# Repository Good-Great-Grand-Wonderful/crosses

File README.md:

> [!NOTE]
> This repo is for historical purposes. Crosses has iterated and is now on [V2](https://github.com/Good-Great-Grand-Wonderful/crosses-v2)

# Crosses

### Gerbers

Production ready and prepped with JLCPCB part numbers: [Gerbers](Gerbers)

### BOM

#### Cases

N = Number of trackballs

| Qty       |3x5 | 3x6 | 4x6 | Item                                              | Notes                             |
|-----------|----|-----|-----|---------------------------------------------------|-----------------------------------|
| 24        | x  | x   | x   | M3 Heat set inserts                               |                                   |
| 16        | x  | x   | x   | M3 x 5mm Hex Bolts                                | +2 for every trackball you delete |
| 2xN       | x  | x   | x   | M3 x 12mm Hex Bolts                               |                                   |
| 2xN       | x  | x   | x   | M3 x 8mm Hex Bolts                                |                                   |
| 1         | x  | x   | x   | Thumb Cluster PCB Panel                           |                                   |
| 4         | x  | x   | x   | Hirose FH12-14S 0.5SH 1x14 1MP P0.50mm Horizontal |                                   |
| 2         | x  | x   | x   | SM06B-SRSS-TB(LF)(SN)                             |                                   |
| 1         | x  |     |     | 3x5 Matrix PCB Panel                              |                                   |
| 1         |    | x   |     | 3x6 Matrix PCB Panel                              |                                   |
| 1         |    |     | x   | 4x6 Matrix PCB Panel                              |                                   |
| 2         | x  | x   | x   | 150mm 14p 0.5mm pitch FFC cables                  |                                   |
| 1xN       | x  | x   | x   | 100mm 6p JST SH 1.0 Same direction cables         |                                   |
| 2x        | x  | x   | x   | Thumb Cluster Case (one should be flipped)        |                                   |
| 2x        | x  |     |     | 3x5 Matrix Case    (one should be flipped)        |                                   |
| 2x        |    | x   |     | 3x6 Matrix Case    (one should be flipped)        |                                   |
| 2x        |    |     | x   | 4x6 Matrix Case    (one should be flipped)        |                                   |
| 36x       | x  |     |     | Kailh Choc Hotswap Sockets                        |                                   |
| 42x       |    | x   |     | Kailh Choc Hotswap Sockets                        |                                   |
| 54x       |    |     | x   | Kailh Choc Hotswap Sockets                        |                                   |
| 36x       | x  |     |     | 1N4148 SMD SOD-123 Resistors                      |                                   |
| 42x       |    | x   |     | 1N4148 SMD SOD-123 Resistors                      |                                   |
| 54x       |    |     | x   | 1N4148 SMD SOD-123 Resistors                      |                                   |
| 2         | x  | x   | x   | Trackball Mount                                   | `models` directory                |
| 1xN       | x  | x   | x   | Trackball PCB                                     |                                   |
| 1xN       | x  | x   | x   | PMW3610                                           |                                   |
| 1xN       | x  | x   | x   | Trackball Carrier Base                            | `models` directory                |
| 1xN       | x  | x   | x   | Trackball Carrier Top                             | `models` directory                |

## License

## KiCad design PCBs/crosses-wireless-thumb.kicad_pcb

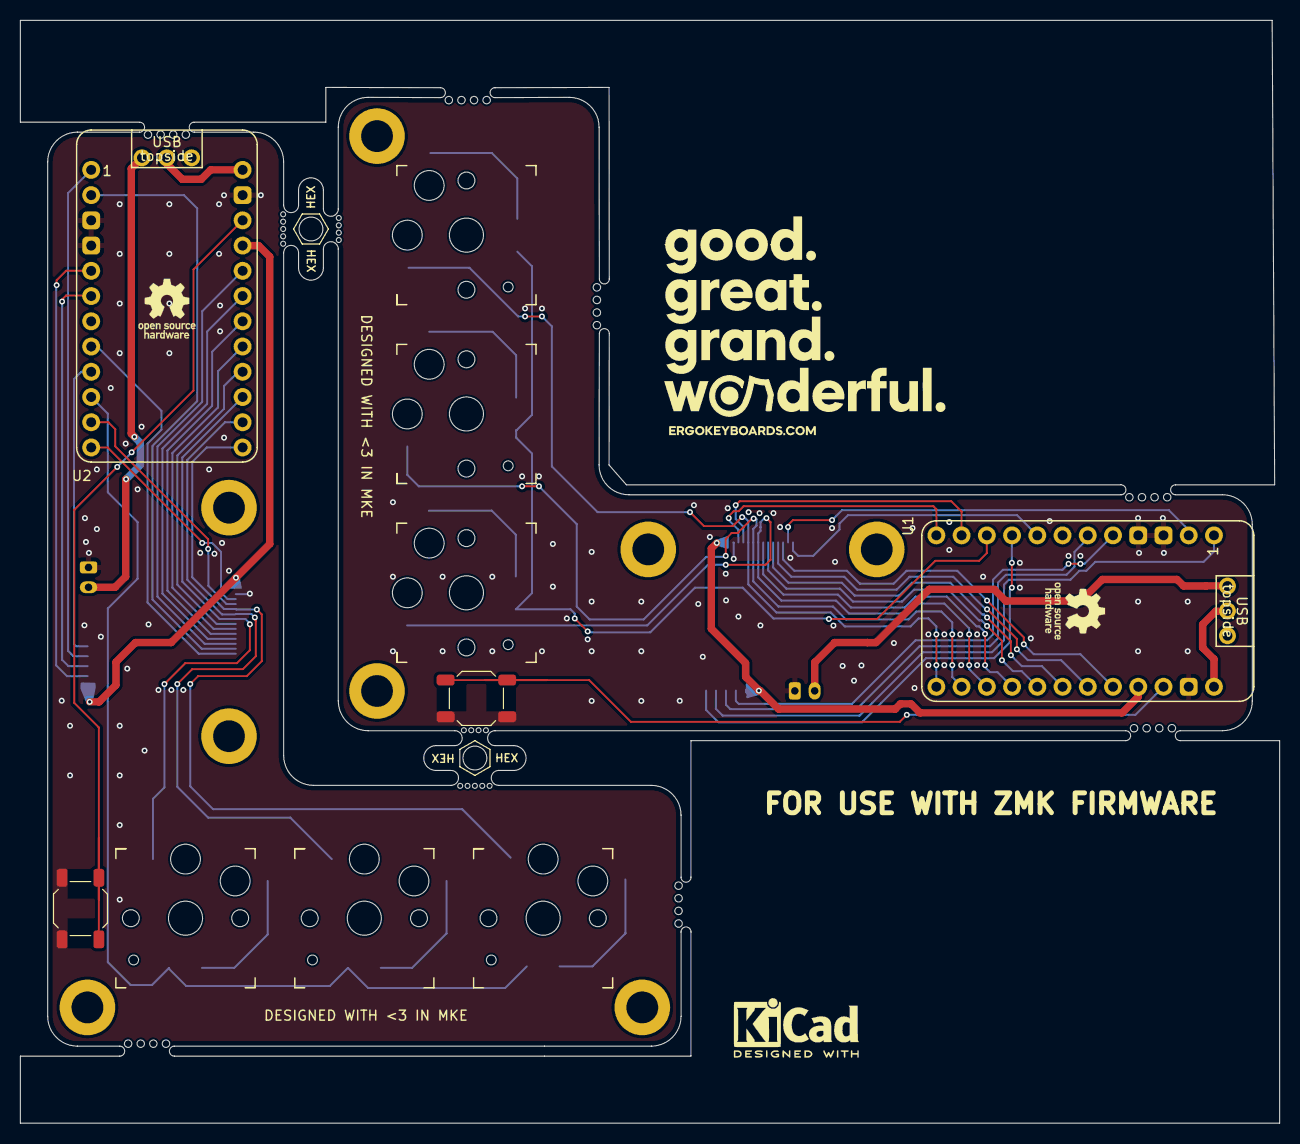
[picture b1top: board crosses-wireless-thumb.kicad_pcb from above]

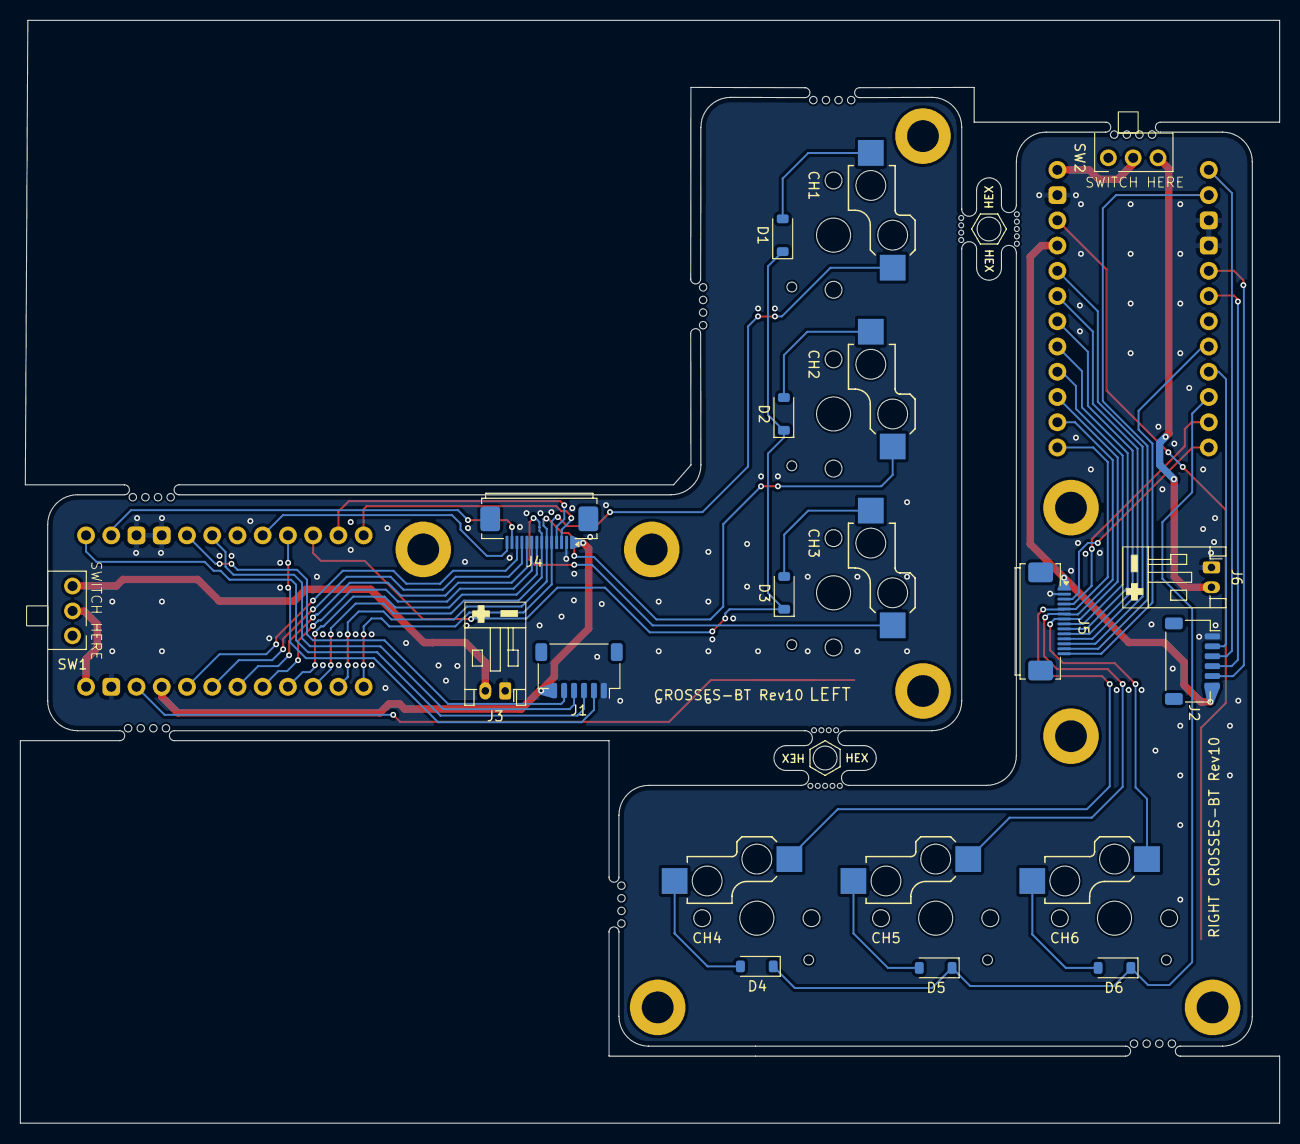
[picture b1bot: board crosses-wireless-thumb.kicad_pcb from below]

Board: 2 copper layers, 126.8 x 111.0 mm, 34 parts (18 on the bottom side), 49 nets.

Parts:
CH1, CH2, CH3, CH4, CH5, CH6: CPG135001S30; Kailh_socket_PG1350
D1, D2, D3, D4, D5, D6: 1N4148; D_SOD-123
H1, H1#2, H2, H2#2, H3, H3#2, H3#3, H3#4: MountingHole; MountingHole_3.2mm_M3_DIN965_Pad
J1, J2: SM06B-SRSS-TB(LF)(SN); JST_SH_SM06B-SRSS-TB_1x06-1MP_P1.00mm_Horizontal
J3, J6: Conn_01x02_Socket; JST_PH_S2B-PH-K_1x02_P2.00mm_Horizontal
J4, J5: Conn_01x14_Pin; XUNPU_FPC-05F-14PH20_1x14-1MP_P0.5mm_Horizontal
MB5, MB5#2: 5.5mm; mousebites_5p5mm_easysnap
SW1, SW2: SW_SPDT; Switch-MK-12D18-G030
SW3, SW4: SW_SPST; SW_SPST_SKQG_WithStem
U1, U2: supermini nrf / nice nano v2; Helios_AH_USBup

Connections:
GND: J1.1, J2.1, J3.1, J4.2, J5.2, J6.1, SW3.1 (A), SW4.2 (B), U1.3 (GND), U1.4 (GND), U1.14 (GND), U2.3 (GND), U2.4 (GND), U2.14 (GND)
L-COL0: J4.9, U1.20 (F7)
L-COL1: J4.8, U1.21 (B1)
L-COL2: CH1.1, J4.5, U1.24 (B6)
L-COL3: CH2.1, J4.6, U1.23 (B2)
L-COL4: CH3.1, J4.7, U1.22 (B3)
L-COLP: J4.13, U1.2 (D2-RX)
L-CS: J1.2, U1.9 (D7)
L-I2C SCL: J4.3, U1.12 (B5)
L-I2C SDA: J4.4, U1.11 (B4)
L-MISO: J1.3, U1.1 (D3-TX)
L-MOSI: J1.4, U1.6 (D0)
L-ROW0: J4.10, U1.19 (F6)
L-ROW1: J4.11, U1.18 (F5)
L-ROW2: J4.12, U1.17 (F4)
L-ROW3: D1.1 (K), D2.1 (K), D3.1 (K), U1.10 (E6)
L-ROWH: J4.14, U1.8 (C6)
L-RST: SW3.2 (B), U1.15 (RST)
L-SCK: J1.5, U1.5 (D1)
L-VCC: J1.6, J4.1, U1.16 (VCC)
unnamed: CH1.2, D1.2 (A)
unnamed: CH2.2, D2.2 (A)
unnamed: CH3.2, D3.2 (A)
unnamed: CH4.2, D4.2 (A)
unnamed: CH5.2, D5.2 (A)
unnamed: CH6.2, D6.2 (A)
unnamed: J3.2, SW1.3 (C)
unnamed: J6.2, SW2.3 (C)
R-COL0: J5.9, U2.20 (F7)
R-COL1: J5.8, U2.21 (B1)
R-COL2: CH4.1, J5.5, U2.24 (B6)
R-COL3: CH5.1, J5.6, U2.23 (B2)
R-COL4: CH6.1, J5.7, U2.22 (B3)
R-COLP: J5.13, U2.2 (D2-RX)
R-CS: J2.2, U2.9 (D7)
R-I2C SCL: J5.3, U2.12 (B5)
R-I2C SDA: J5.4, U2.11 (B4)
R-MISO: J2.3, U2.1 (D3-TX)
R-MOSI: J2.4, U2.6 (D0)
R-ROW0: J5.10, U2.19 (F6)
R-ROW1: J5.11, U2.18 (F5)
R-ROW2: J5.12, U2.17 (F4)
R-ROW3: D4.1 (K), D5.1 (K), D6.1 (K), U2.10 (E6)
R-ROWH: J5.14, U2.8 (C6)
R-RST: SW4.1 (A), U2.15 (RST)
R-SCK: J2.5, U2.5 (D1)
R-VCC: J2.6, J5.1, U2.16 (VCC)
VBATTL: SW1.2 (B), U1.13 (B0)
VBATTR: SW2.2 (B), U2.13 (B0)

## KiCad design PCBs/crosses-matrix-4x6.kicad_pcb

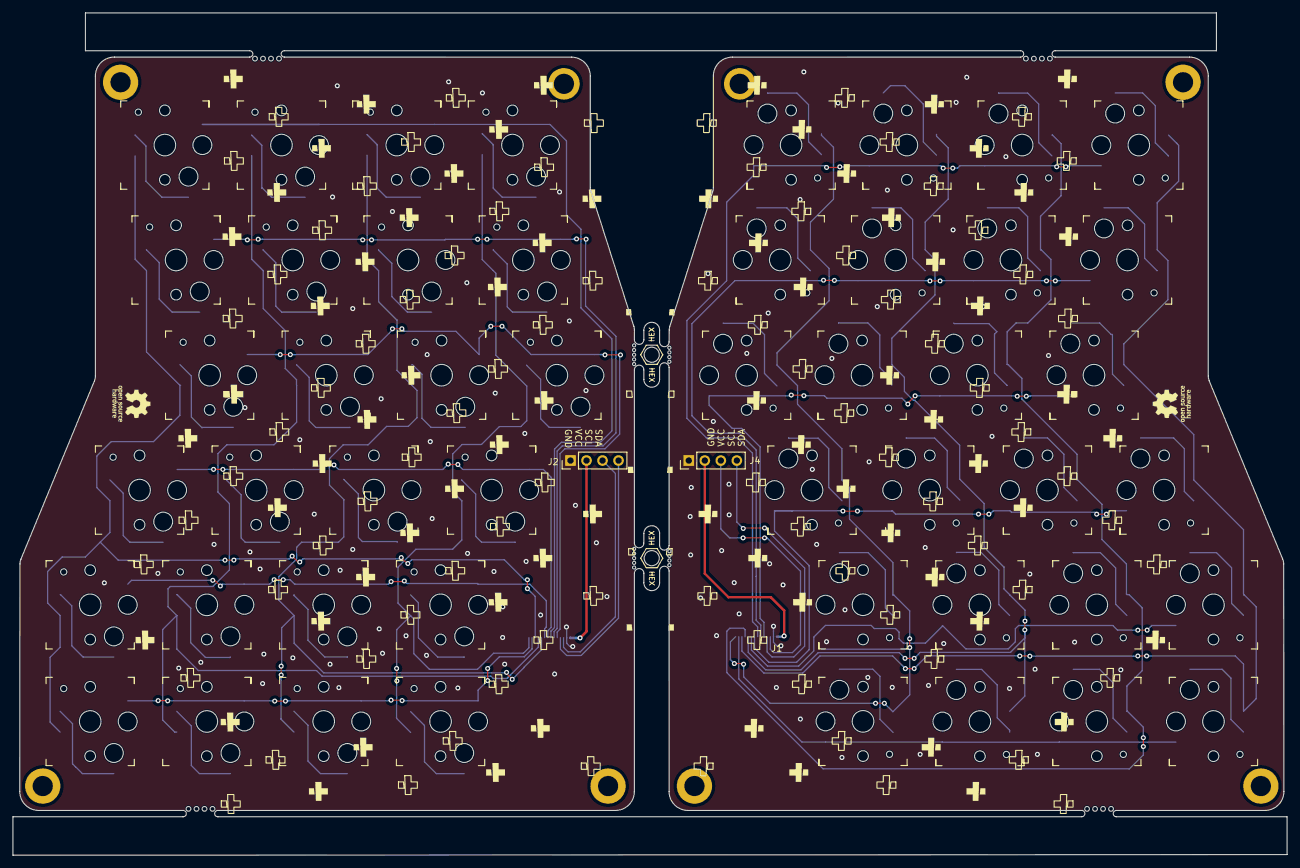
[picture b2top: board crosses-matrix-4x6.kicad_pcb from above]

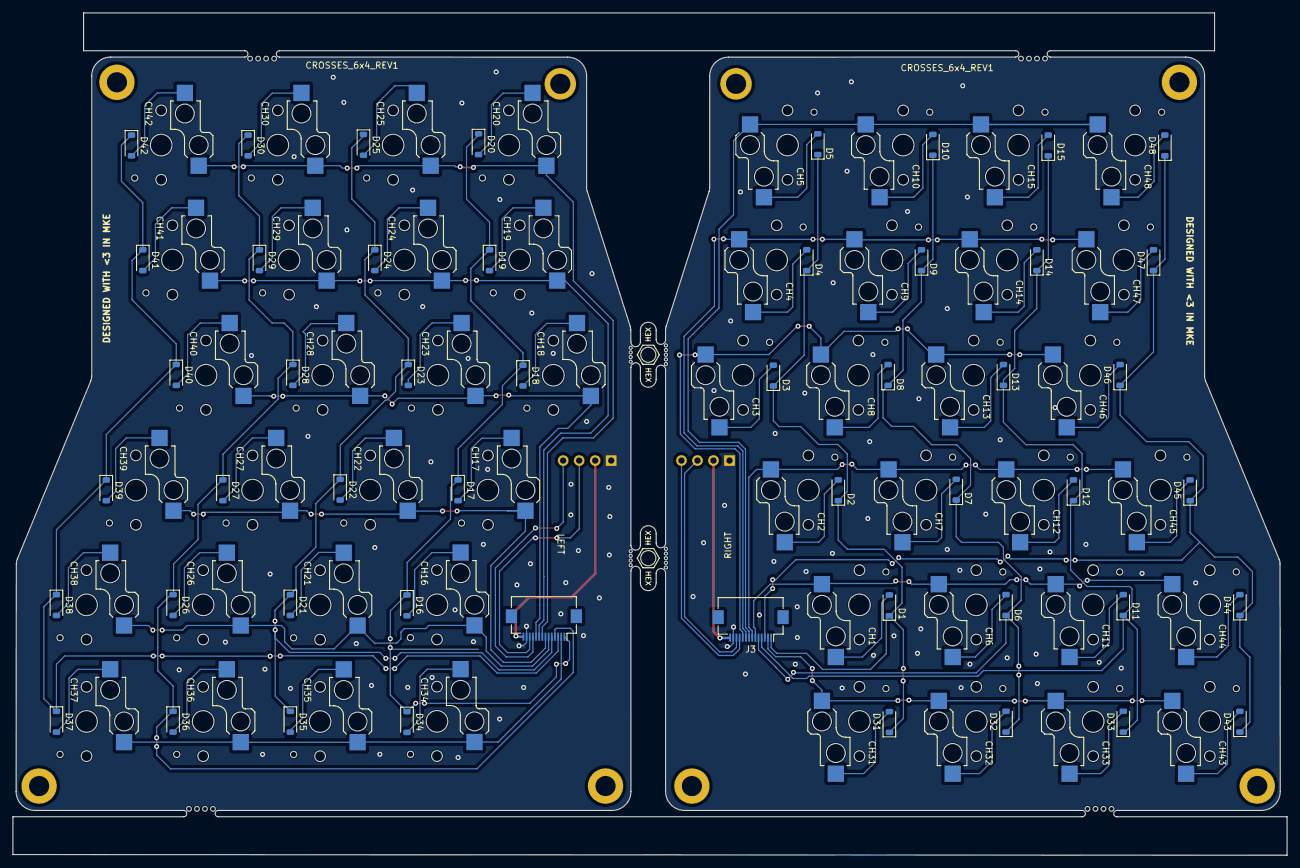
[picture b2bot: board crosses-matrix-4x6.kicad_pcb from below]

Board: 2 copper layers, 202.1 x 133.6 mm, 110 parts (54 on the bottom side), 75 nets.

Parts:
CH1, CH2, CH3, CH4, CH5, CH6, CH7, CH8, CH9, CH10, CH11, CH12, CH13, CH14, CH15, CH16, CH17, CH18, CH19, CH20, CH21, CH22, CH23, CH24, CH25, CH26, CH27, CH28, CH29, CH30, CH31, CH32, CH33, CH34, CH35, CH36, CH37, CH38, CH39, CH40, CH41, CH42, CH43, CH44, CH45, CH46, CH47, CH48: CPG135001S30; Kailh_socket_PG1350
D1, D2, D3, D4, D5, D6, D7, D8, D9, D10, D11, D12, D13, D14, D15, D16, D17, D18, D19, D20, D21, D22, D23, D24, D25, D26, D27, D28, D29, D30, D31, D32, D33, D34, D35, D36, D37, D38, D39, D40, D41, D42, D43, D44, D45, D46, D47, D48: 1N4148; D_SOD-123
H1, H1#2, H3, H3#2, H5, H5#2, H6, H6#2: MountingHole; MountingHole_3.2mm_M3_DIN965_Pad
J1, J3: Conn_01x14_Pin; Hirose_FH12-14S-0.5SH_1x14-1MP_P0.50mm_Horizontal
J2, J4: Conn_01x04_Socket; PinHeader_1x04_P2.54mm_Vertical
MB5, MB5#2: 5.5mm; mousebites_5p5mm_easysnap

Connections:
GND: J1.13, J2.1, J3.13, J4.1
L-COL0: CH1.1, CH6.1, CH11.1, CH44.1, J3.6
L-COL1: CH2.1, CH7.1, CH12.1, CH45.1, J3.7
L-COL2: CH3.1, CH8.1, CH13.1, CH46.1, J3.10
L-COL3: CH4.1, CH9.1, CH14.1, CH47.1, J3.9
L-COL4: CH5.1, CH10.1, CH15.1, CH48.1, J3.8
L-COLP: CH31.1, CH32.1, CH33.1, CH43.1, J3.2
L-ROW0: D6.1 (K), D7.1 (K), D8.1 (K), D9.1 (K), D10.1 (K), D32.1 (K), J3.5
L-ROW1: D11.1 (K), D12.1 (K), D13.1 (K), D14.1 (K), D15.1 (K), D33.1 (K), J3.4
L-ROW2: D43.1 (K), D44.1 (K), D45.1 (K), D46.1 (K), D47.1 (K), D48.1 (K), J3.3
L-ROW-N1: D1.1 (K), D2.1 (K), D3.1 (K), D4.1 (K), D5.1 (K), D31.1 (K), J3.1
unnamed: CH1.2, D1.2 (A)
unnamed: CH2.2, D2.2 (A)
unnamed: CH3.2, D3.2 (A)
unnamed: CH4.2, D4.2 (A)
unnamed: CH5.2, D5.2 (A)
unnamed: CH6.2, D6.2 (A)
unnamed: CH7.2, D7.2 (A)
unnamed: CH8.2, D8.2 (A)
unnamed: CH9.2, D9.2 (A)
unnamed: CH10.2, D10.2 (A)
unnamed: CH11.2, D11.2 (A)
unnamed: CH12.2, D12.2 (A)
unnamed: CH13.2, D13.2 (A)
unnamed: CH14.2, D14.2 (A)
unnamed: CH15.2, D15.2 (A)
unnamed: CH16.2, D16.2 (A)
unnamed: CH17.2, D17.2 (A)
unnamed: CH18.2, D18.2 (A)
unnamed: CH19.2, D19.2 (A)
unnamed: CH20.2, D20.2 (A)
unnamed: CH21.2, D21.2 (A)
unnamed: CH22.2, D22.2 (A)
unnamed: CH23.2, D23.2 (A)
unnamed: CH24.2, D24.2 (A)
unnamed: CH25.2, D25.2 (A)
unnamed: CH26.2, D26.2 (A)
unnamed: CH27.2, D27.2 (A)
unnamed: CH28.2, D28.2 (A)
unnamed: CH29.2, D29.2 (A)
unnamed: CH30.2, D30.2 (A)
unnamed: CH31.2, D31.2 (A)
unnamed: CH32.2, D32.2 (A)
unnamed: CH33.2, D33.2 (A)
unnamed: CH34.2, D34.2 (A)
unnamed: CH35.2, D35.2 (A)
unnamed: CH36.2, D36.2 (A)
unnamed: CH37.2, D37.2 (A)
unnamed: CH38.2, D38.2 (A)
unnamed: CH39.2, D39.2 (A)
unnamed: CH40.2, D40.2 (A)
unnamed: CH41.2, D41.2 (A)
unnamed: CH42.2, D42.2 (A)
unnamed: CH43.2, D43.2 (A)
unnamed: CH44.2, D44.2 (A)
unnamed: CH45.2, D45.2 (A)
unnamed: CH46.2, D46.2 (A)
unnamed: CH47.2, D47.2 (A)
unnamed: CH48.2, D48.2 (A)
R-COL0: CH16.1, CH21.1, CH26.1, CH38.1, J1.6
R-COL1: CH17.1, CH22.1, CH27.1, CH39.1, J1.7
R-COL2: CH18.1, CH23.1, CH28.1, CH40.1, J1.10
R-COL3: CH19.1, CH24.1, CH29.1, CH41.1, J1.9
R-COL4: CH20.1, CH25.1, CH30.1, CH42.1, J1.8
R-COLP: CH34.1, CH35.1, CH36.1, CH37.1, J1.2
R-ROW0: D21.1 (K), D22.1 (K), D23.1 (K), D24.1 (K), D25.1 (K), D35.1 (K), J1.5
R-ROW1: D26.1 (K), D27.1 (K), D28.1 (K), D29.1 (K), D30.1 (K), D36.1 (K), J1.4
R-ROW2: D37.1 (K), D38.1 (K), D39.1 (K), D40.1 (K), D41.1 (K), D42.1 (K), J1.3
R-ROW-N1: D16.1 (K), D17.1 (K), D18.1 (K), D19.1 (K), D20.1 (K), D34.1 (K), J1.1
SCL: J2.3, J3.12
SCL-R: J1.12, J4.3
SDA: J2.4, J3.11
SDA-R: J1.11, J4.4
VCC: J2.2, J3.14
VCC-R: J1.14, J4.2

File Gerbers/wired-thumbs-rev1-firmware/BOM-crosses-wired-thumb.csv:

Comment,Designator,Footprint,LCSC,Quantity
TYPE-C-31-M-12 USB,"P1,P2",USB_C_Receptacle_HRO_TYPE-C-31-M-12,C165948,2
Conn_01x14_Pin,"J4,J5",Hirose_FH12-14S-0.5SH_1x14-1MP_P0.50mm_Horizontal,C5378715,2
1N4148,"D1,D2,D3,D4,D5,D6",D_SOD-123,C81598,6
MountingHole,H3,MountingHole_3.2mm_M3_DIN965_Pad,,1
MountingHole,H1,MountingHole_3.2mm_M3_DIN965_Pad,,1
MountingHole,H2,MountingHole_3.2mm_M3_DIN965_Pad,,1

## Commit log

2025-08-03 Adding trackball models
    Adding static carrier
2025-09-14 Tweaking thumbcluster
2025-09-28 Crosses trackball mount fine tuning
2025-10-02 Adding wireless thumb cases
2025-10-03 Update README.md
    Change mentions from 3mm to M3
2025-11-11 No modifications needed for wireless
2025-11-24 Better geometry for trackball mount
2025-11-24 Improve bridges trackball mount
2025-11-24 Adding explicit left/right models
2025-11-24 Explicit left/right thumbclusters
2025-11-24 Update firmware links in README
    Removed outdated firmware links and added ZMK link.
2025-11-24 Update FFC cables and trackball components in README
2025-11-27 Add small spherical guard to stop excess movement.
    Harder to print, and somewhat fragile until a trackball is inserted.
    Inserting a trackball only takes a small push, no risk of damage.
2025-11-29 Move the trackball guard stl file to a mod folder.
    At the request of the primary author, this commit moves the trackball
    guard file to a new folder that distinguishes this as a modificatiohn to
    the originaal desgn.
2025-11-29 Reorganizing
2025-12-29 Adding clearance on right mount
2026-01-15 feat: Introduce trackball retainer mod with documentation and 3D model for Crosses/Bridges keyboards.
2026-01-19 Adding adjustable experiment
2026-03-19 Fixup old release
2026-05-26 Changing license, adding wireless Gerbers, PCBs, etc
2026-05-26 License graphic
2026-06-29 Revise README for historical context and V2 link
    Updated README to indicate repository is for historical purposes and linked to V2.
2026-06-30 Update README to reflect new repository version

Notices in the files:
README.md:
License:
CC BY-SA 4.0
